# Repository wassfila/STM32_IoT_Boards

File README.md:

# STM32_IoT_Boards
* Expansion boards, PCB designs with STM32 chips.
* firmware running mbed-os
* simplest mesh ever with c++ driver libraries, rf-mesh lib using an nrf24l01+ lib

# Progress
* PCBs are under test
* 24 PIO ULN on/off test successfull
* Still no noticed design issues
* Current struggle with the PA3,PA2 ports that do not output the PWM as configured for a default UART
* Sensors node already working fine as an RF-Dongle (sensors not tested yet)
* Soldering order of nrf and bluepill is very important !!! Soldering order strategy required as it is double sided board.

# Git Submodules
* Still struggling with submodules, do not forget either of recursive clone, or manual add of submodule for pilibs

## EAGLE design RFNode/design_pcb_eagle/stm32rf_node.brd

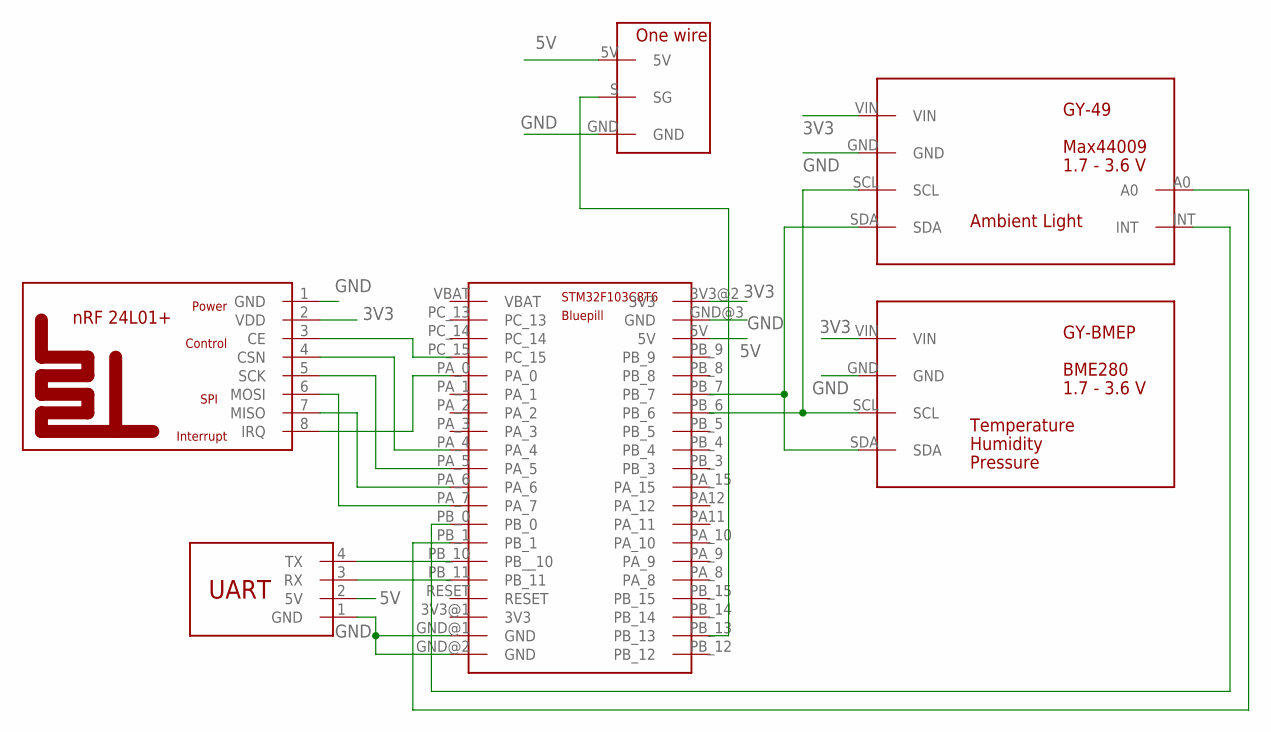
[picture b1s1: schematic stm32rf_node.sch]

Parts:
U$1: STM32_BLUEPILL
U$2: NRF24L01+REFDESIGNMINI; NRF24L01+REFDESIGN-MINI
U$3: GY-BMEPGY-BMEP-NOHOLE; GY-BMEP-NOHOLE
U$4: GY-49G-49-SURF; GY-49-SURF
U$5: ONE_WIRE'RIGHT'; ONE_WIRE_RIGHT
U$6: UARTMINI; UART-MINI

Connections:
3V3: U$1.3V3@2 (3V3), U$2.2 (VDD), U$3.VIN, U$4.VIN
5V: U$1.5V, U$5.5V, U$6.2 (5V); also elsewhere on the board
GND: U$1.GND@1 (GND), U$1.GND@2 (GND), U$1.GND@3 (GND), U$2.1 (GND), U$3.GND, U$4.GND, U$5.GND, U$6.1 (GND); also elsewhere on the board
INT: U$1.PB_0, U$4.INT
unnamed: U$1.PA_7, U$2.6 (MOSI)
unnamed: U$1.PA_6, U$2.7 (MISO)
unnamed: U$1.PA_5, U$2.5 (SCK)
unnamed: U$1.PA_4, U$2.4 (CSN)
unnamed: U$1.PB_1, U$4.A0
unnamed: U$1.PA_0, U$2.8 (IRQ)
unnamed: U$1.PB_10 (PB__10), U$6.4 (TX)
unnamed: U$1.PB_11, U$6.3 (RX)
unnamed: U$1.PB_6, U$3.SCL, U$4.SCL
unnamed: U$1.PB_7, U$3.SDA, U$4.SDA
unnamed: U$1.PC_15, U$2.3 (CE)
unnamed: U$1.PB_13, U$5.S (SG)

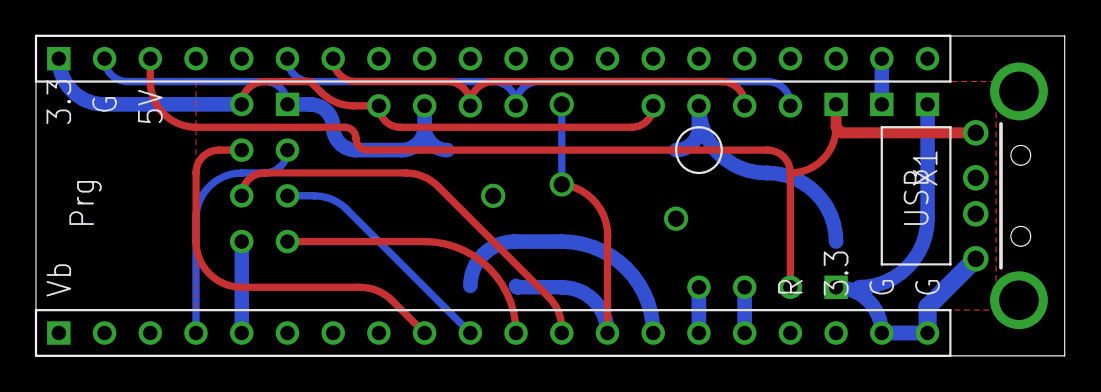
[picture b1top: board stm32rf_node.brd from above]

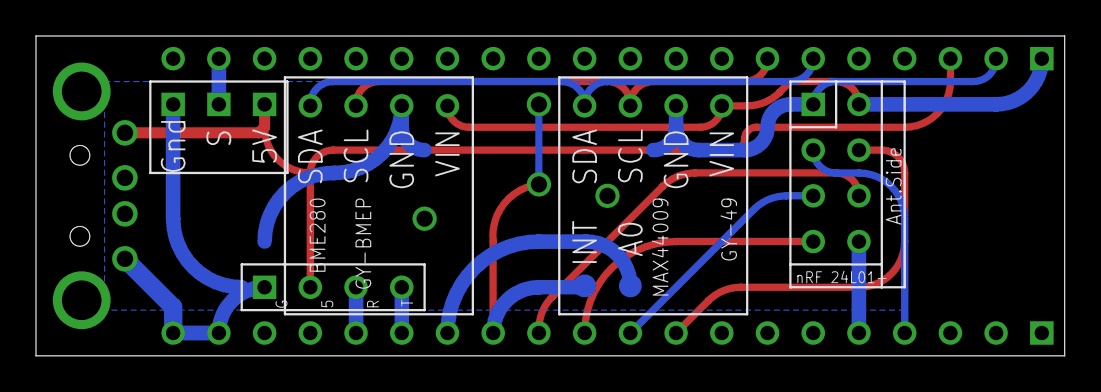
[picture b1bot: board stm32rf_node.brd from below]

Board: 2 copper layers, 57.1 x 17.8 mm, 7 parts (5 on the bottom side), 16 nets.

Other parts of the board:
X1: USB-A-H

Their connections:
5V: X1.VBUS; also elsewhere on the board
GND: X1.GND; also elsewhere on the board

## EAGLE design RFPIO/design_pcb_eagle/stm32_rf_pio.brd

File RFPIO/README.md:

# design_pcb_eagle

# firmware
* STM32 
* Bluepill as target
* mbed-os

# picpp_control
* Raspberry pi c++ control code that communicates with the Dongle firmware (not this one, rather the one under RFNode) through serial port
* This firmware is expecting RF messages coming from a dongle

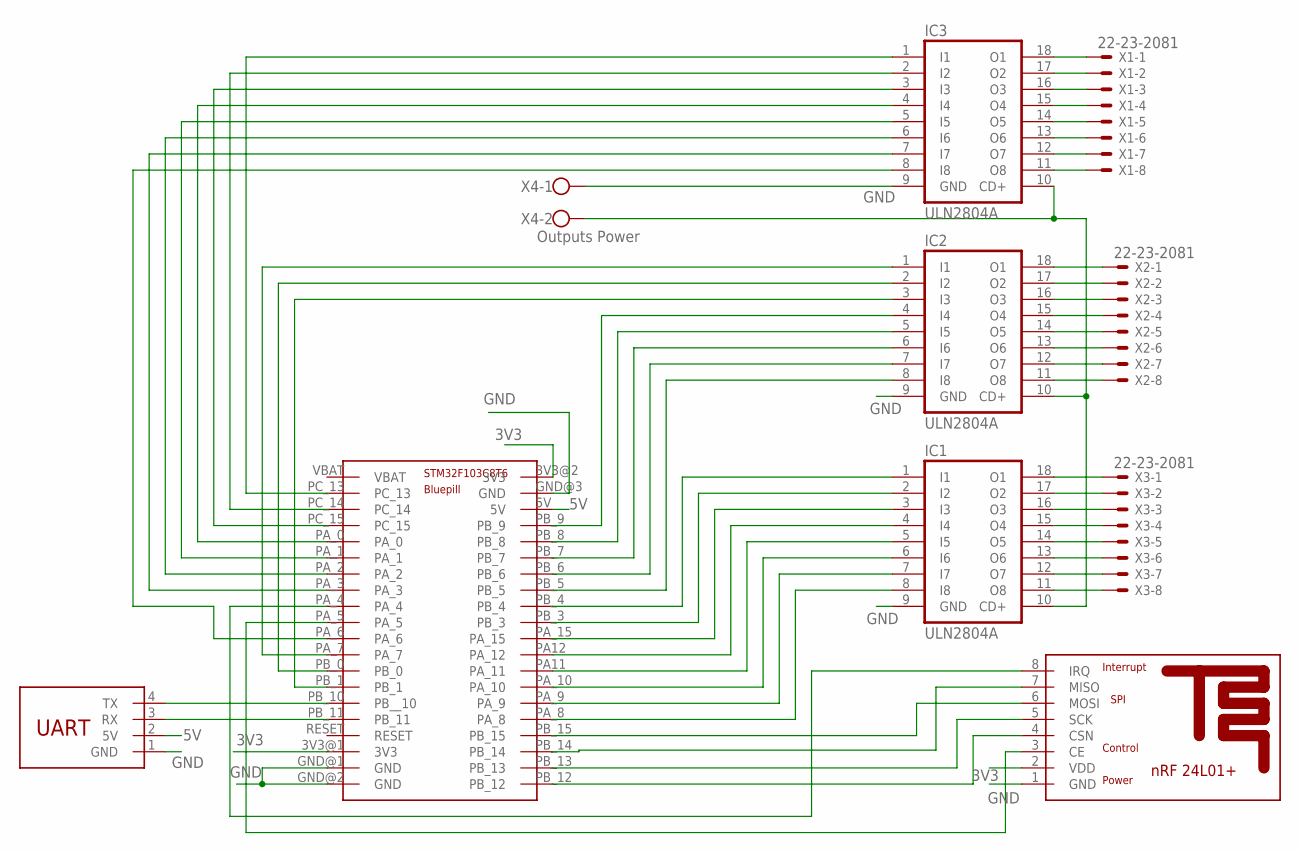
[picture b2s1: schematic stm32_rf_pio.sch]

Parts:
IC1, IC2, IC3: ULN2804A; DIL18
U$1: STM32_BLUEPILL
U$2: NRF24L01+REFDESIGNMINI; NRF24L01+REFDESIGN-MINI
U$3: UARTMINI; UART-MINI
X1, X2, X3: 22-23-2081
X4: Outputs Power; W237-102

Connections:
3V3: U$1.3V3@1 (3V3), U$1.3V3@2 (3V3), U$2.2 (VDD)
5V: U$1.5V, U$3.2 (5V)
A12: IC1.4 (I4), U$1.PA12 (PA_12)
GND: IC1.9 (GND), IC2.9 (GND), IC3.9 (GND), U$1.GND@1 (GND), U$1.GND@2 (GND), U$1.GND@3 (GND), U$2.1 (GND), U$3.1 (GND), X4.1
HV: IC1.10 (CD+), IC2.10 (CD+), IC3.10 (CD+), X4.2
M11: IC1.8 (I8), U$1.PA_8
M12: IC1.7 (I7), U$1.PA_9
M13: IC1.6 (I6), U$1.PA_10
M14: IC1.5 (I5), U$1.PA11 (PA_11)
M21: IC1.3 (I3), U$1.PA_15
M22: IC1.2 (I2), U$1.PB_3
M23: IC3.6 (I6), U$1.PA_2
M24: IC3.7 (I7), U$1.PA_3
M31: IC1.1 (I1), U$1.PB_4
M32: IC2.8 (I8), U$1.PB_5
M33: IC2.2 (I2), U$1.PB_0
M34: IC2.3 (I3), U$1.PB_1
unnamed: U$1.PB_12, U$2.4 (CSN)
unnamed: U$1.PB_13, U$2.5 (SCK)
unnamed: U$1.PB_14, U$2.7 (MISO)
unnamed: U$1.PB_15, U$2.6 (MOSI)
unnamed: IC2.7 (I7), U$1.PB_6
unnamed: IC2.6 (I6), U$1.PB_7
unnamed: IC2.5 (I5), U$1.PB_8
unnamed: IC2.4 (I4), U$1.PB_9
unnamed: IC2.1 (I1), U$1.PA_7
unnamed: IC3.18 (O1), X1.1
unnamed: IC3.17 (O2), X1.2
unnamed: IC3.16 (O3), X1.3
unnamed: IC3.4 (I4), U$1.PA_0
unnamed: IC3.5 (I5), U$1.PA_1
unnamed: IC3.8 (I8), U$1.PA_6
unnamed: IC3.1 (I1), U$1.PC_13
unnamed: IC3.2 (I2), U$1.PC_14
unnamed: IC3.3 (I3), U$1.PC_15
unnamed: IC3.15 (O4), X1.4
unnamed: IC3.14 (O5), X1.5
unnamed: IC3.13 (O6), X1.6
unnamed: IC3.12 (O7), X1.7
unnamed: IC3.11 (O8), X1.8
unnamed: IC2.18 (O1), X2.1
unnamed: IC2.17 (O2), X2.2
unnamed: IC2.16 (O3), X2.3
unnamed: IC2.15 (O4), X2.4
unnamed: IC2.14 (O5), X2.5
unnamed: IC2.13 (O6), X2.6
unnamed: IC2.12 (O7), X2.7
unnamed: IC2.11 (O8), X2.8
unnamed: IC1.18 (O1), X3.1
unnamed: IC1.17 (O2), X3.2
unnamed: IC1.16 (O3), X3.3
unnamed: IC1.15 (O4), X3.4
unnamed: IC1.14 (O5), X3.5
unnamed: IC1.13 (O6), X3.6
unnamed: IC1.12 (O7), X3.7
unnamed: IC1.11 (O8), X3.8
unnamed: U$1.PA_4, U$2.8 (IRQ)
unnamed: U$1.PA_5, U$2.3 (CE)
unnamed: U$1.PB_10 (PB__10), U$3.4 (TX)
unnamed: U$1.PB_11, U$3.3 (RX)

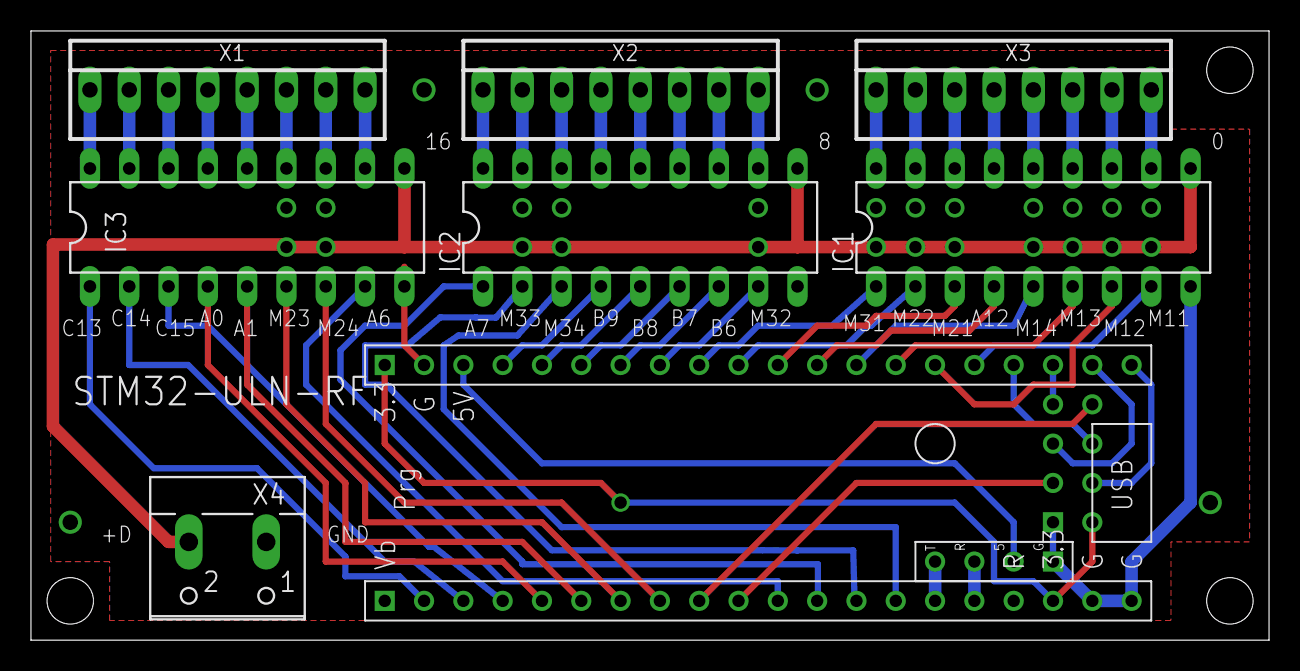
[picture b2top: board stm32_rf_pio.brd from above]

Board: 2 copper layers, 80.0 x 39.4 mm, 10 parts (1 on the bottom side), 60 nets.

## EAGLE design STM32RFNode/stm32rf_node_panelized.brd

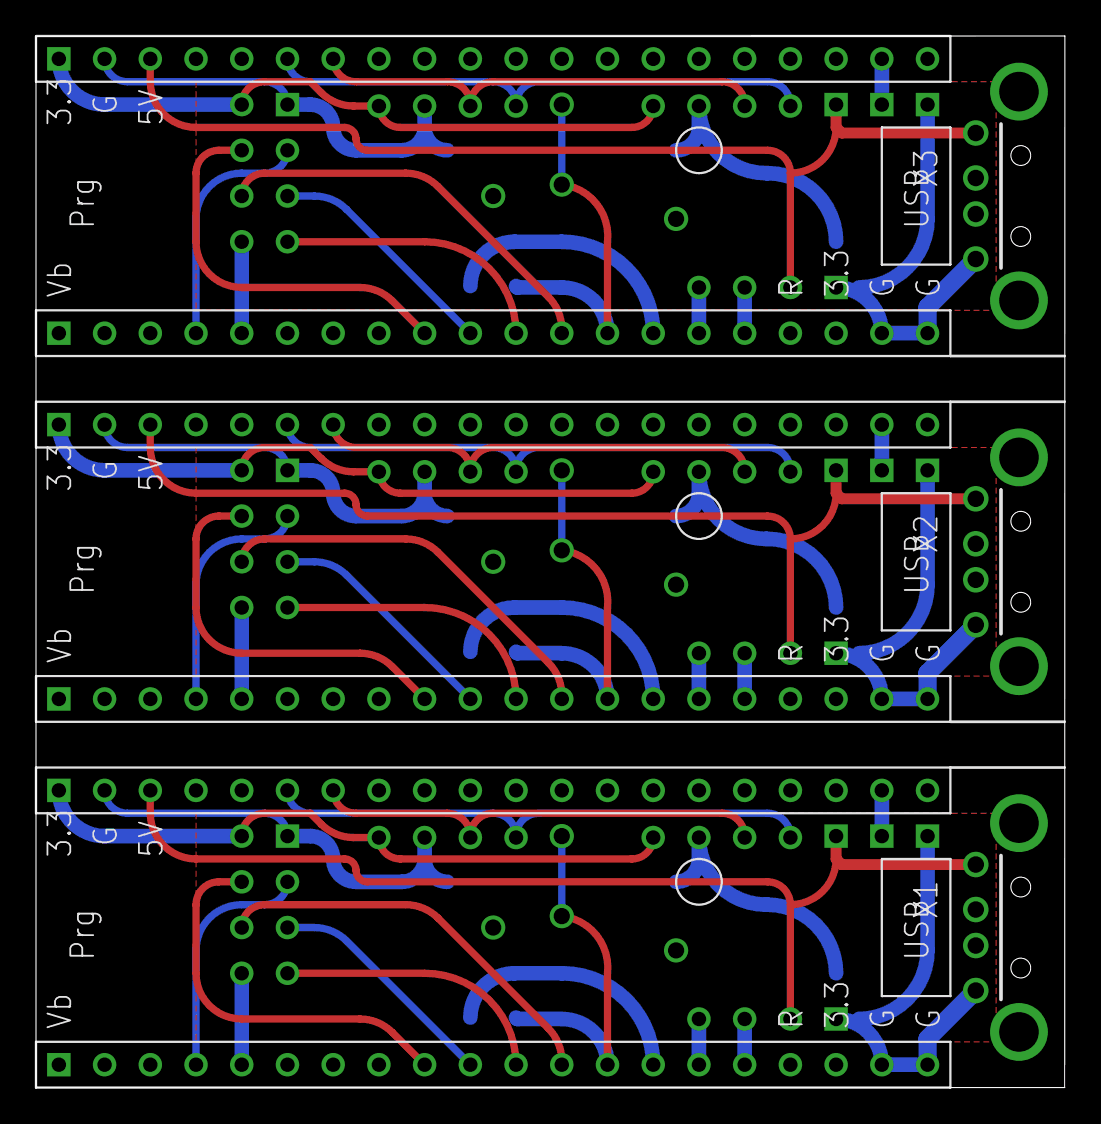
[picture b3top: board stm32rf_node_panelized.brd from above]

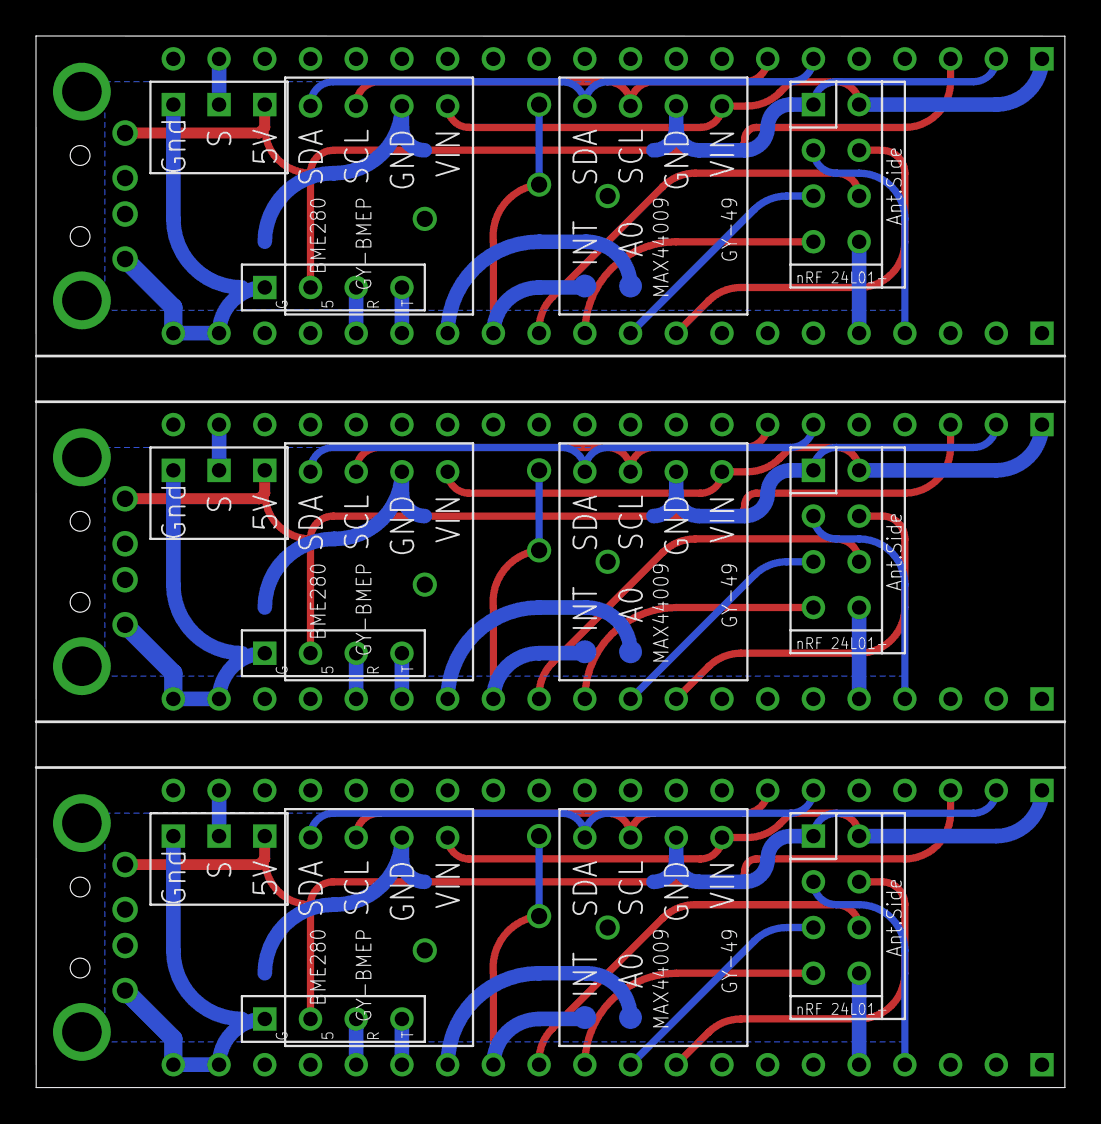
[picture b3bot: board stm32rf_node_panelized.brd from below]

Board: 2 copper layers, 57.2 x 58.4 mm, 21 parts (15 on the bottom side), 48 nets.

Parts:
U$1, U$7, U$13: STM32_BLUEPILL
U$2, U$8, U$14: NRF24L01+REFDESIGNMINI; NRF24L01+REFDESIGN-MINI
U$3, U$9, U$15: GY-BMEPGY-BMEP-NOHOLE; GY-BMEP-NOHOLE
U$4, U$10, U$16: GY-49G-49-SURF; GY-49-SURF
U$5, U$11, U$17: ONE_WIRE'RIGHT'; ONE_WIRE_RIGHT
U$6, U$12, U$18: UARTMINI; UART-MINI
X1, X2, X3: USB-A-H

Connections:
3V1: U$7.3V3@2, U$8.2, U$9.VIN, U$10.VIN
3V2: U$13.3V3@2, U$14.2, U$15.VIN, U$16.VIN
3V3: U$1.3V3@2, U$2.2, U$3.VIN, U$4.VIN
5V: U$1.5V, U$5.5V, U$6.2, X1.VBUS
5V1: U$7.5V, U$11.5V, U$12.2, X2.VBUS
5V2: U$13.5V, U$17.5V, U$18.2, X3.VBUS
GND: U$1.GND@1, U$1.GND@2, U$1.GND@3, U$2.1, U$3.GND, U$4.GND, U$5.GND, U$6.1, X1.GND
GND1: U$7.GND@1, U$7.GND@2, U$7.GND@3, U$8.1, U$9.GND, U$10.GND, U$11.GND, U$12.1, X2.GND
GND2: U$13.GND@1, U$13.GND@2, U$13.GND@3, U$14.1, U$15.GND, U$16.GND, U$17.GND, U$18.1, X3.GND
INT: U$1.PB_0, U$4.INT
INT1: U$7.PB_0, U$10.INT
INT2: U$13.PB_0, U$16.INT
unnamed: U$1.PA_7, U$2.6
unnamed: U$1.PA_6, U$2.7
unnamed: U$1.PA_5, U$2.5
unnamed: U$1.PA_4, U$2.4
unnamed: U$1.PB_1, U$4.A0
unnamed: U$1.PA_0, U$2.8
unnamed: U$1.PB_10, U$6.4
unnamed: U$1.PB_11, U$6.3
unnamed: U$1.PB_6, U$3.SCL, U$4.SCL
unnamed: U$1.PB_7, U$3.SDA, U$4.SDA
unnamed: U$1.PC_15, U$2.3
unnamed: U$1.PB_13, U$5.S
unnamed: U$7.PB_10, U$12.4
unnamed: U$7.PB_11, U$12.3
unnamed: U$7.PB_6, U$9.SCL, U$10.SCL
unnamed: U$7.PB_7, U$9.SDA, U$10.SDA
unnamed: U$7.PA_7, U$8.6
unnamed: U$7.PA_6, U$8.7
unnamed: U$7.PA_5, U$8.5
unnamed: U$7.PA_4, U$8.4
unnamed: U$7.PB_1, U$10.A0
unnamed: U$7.PA_0, U$8.8
unnamed: U$7.PC_15, U$8.3
unnamed: U$7.PB_13, U$11.S
unnamed: U$13.PB_10, U$18.4
unnamed: U$13.PB_11, U$18.3
unnamed: U$13.PB_6, U$15.SCL, U$16.SCL
unnamed: U$13.PB_7, U$15.SDA, U$16.SDA
unnamed: U$13.PA_7, U$14.6
unnamed: U$13.PA_6, U$14.7
unnamed: U$13.PA_5, U$14.5
unnamed: U$13.PA_4, U$14.4
unnamed: U$13.PB_1, U$16.A0
unnamed: U$13.PA_0, U$14.8
unnamed: U$13.PC_15, U$14.3
unnamed: U$13.PB_13, U$17.S

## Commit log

2017-04-23 First versions of the IoT boards
2017-04-23 Added connections for servo motors with Gnd-HV-Signal for all pwm outputs
2017-04-23 gnd with rastnet
2017-04-24 rounting step 1
2017-04-24 done routing with gnd rastnet
2017-05-06 Added possibility to connect the MPU 6050 on the I2C by shifting connections to match Add with Gnd
2017-05-07 preparing production 1
2017-05-07 First produced version
2017-05-07 First Production with Panel
2017-05-28 updated board
2017-05-28 rename restructure creation of new projects ...
2017-05-28 updated firmware working and testing pi
2017-05-28 ignoregit status
2017-05-28 updated wrog merge after move
2017-05-28 first main testing on off
2017-05-28 first working full pio chain
2017-05-28 Rename firmwareREADME.md to README.md
2017-05-28 moved readme
2017-05-31 renaming project for split pio servos
2017-05-31 new project specific for servos
2017-05-31 testing
2017-06-01 adapted to servos but only 10 work
2017-06-03 testing servos 11,12
2017-09-17 servo fix and rf protocol with CRC
2018-02-11 new production with usb connector
